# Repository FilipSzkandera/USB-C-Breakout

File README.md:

# USB-C Breakout board

I have searched a few places on internet and wasn't able to find a small, cheap and breadboard friendly USB-C adapter that I would like, so I made my own.
It has a neat fanout of all the USB-C pins (without the shield), which are nicely labeled for a very easy use while prototyping.

## Possible usecases:
#### On breadboard:

#### Directly on a prototyping board or a PCB:

## Check out my other PCBs:

- **ESP32-C3 Nano** (in collaboration with [@frycaktadeas](https://github.com/frycaktadeas/)): https://github.com/frycaktadeas/esp32-c3

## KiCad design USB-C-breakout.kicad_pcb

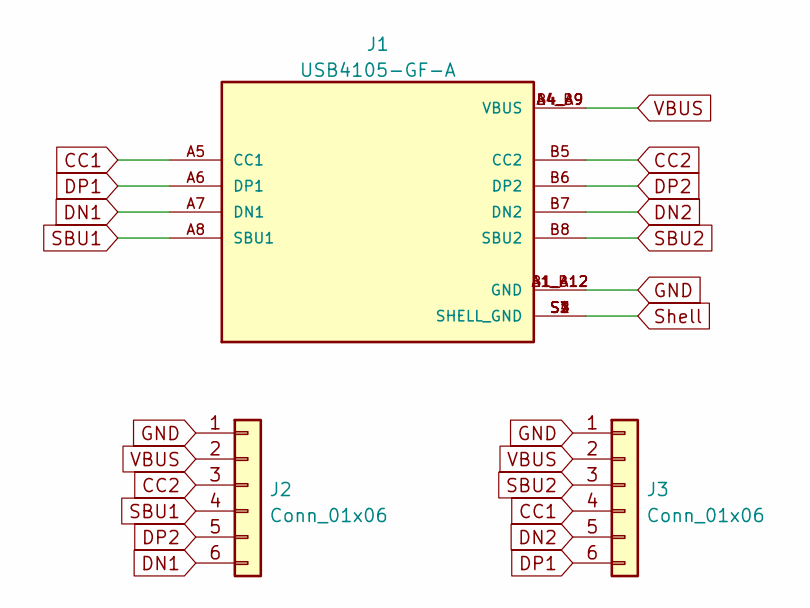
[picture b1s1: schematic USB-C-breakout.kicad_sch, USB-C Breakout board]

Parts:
J1: USB4105-GF-A; GCT_USB4105-GF-A; PARTREV A3
J2, J3: Conn_01x06; PinHeader_1x06_P2.54mm_Vertical

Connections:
CC1: J1.A5 (CC1), J3.4
CC2: J1.B5 (CC2), J2.3
DN1: J1.A7 (DN1), J2.6
DN2: J1.B7 (DN2), J3.5
DP1: J1.A6 (DP1), J3.6
DP2: J1.B6 (DP2), J2.5
GND: J1.A1_B12 (GND), J1.B1_A12 (GND), J2.1, J3.1
SBU1: J1.A8 (SBU1), J2.4
SBU2: J1.B8 (SBU2), J3.3
Shell: J1.S1 (SHELL_GND), J1.S2 (SHELL_GND), J1.S3 (SHELL_GND), J1.S4 (SHELL_GND)
VBUS: J1.A4_B9 (VBUS), J1.B4_A9 (VBUS), J2.2, J3.2

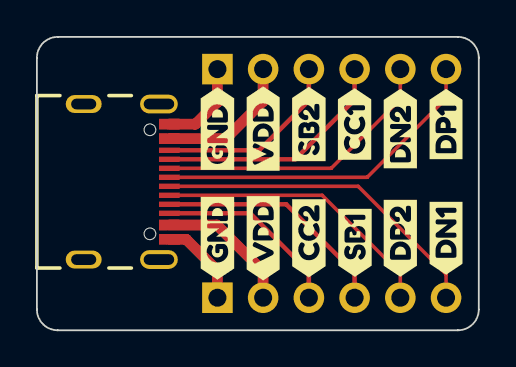
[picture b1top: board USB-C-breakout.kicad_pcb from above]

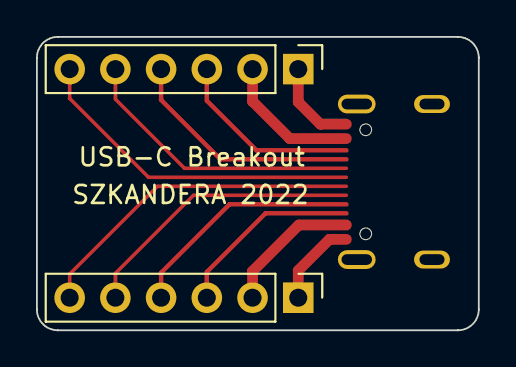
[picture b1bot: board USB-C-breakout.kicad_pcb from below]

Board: 2 copper layers, 24.5 x 16.3 mm, 15 parts (2 on the bottom side), 11 nets.

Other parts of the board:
kibuzzard-62B9BCC1: G***; kibuzzard-62B9BCC1
kibuzzard-62B9BCFF: G***; kibuzzard-62B9BCFF
kibuzzard-62B9BD52: G***; kibuzzard-62B9BD52
kibuzzard-62B9BD67: G***; kibuzzard-62B9BD67
kibuzzard-62B9BD75: G***; kibuzzard-62B9BD75
kibuzzard-62B9BDB7: G***; kibuzzard-62B9BDB7
kibuzzard-62B9BDD1: G***; kibuzzard-62B9BDD1
kibuzzard-62B9BDF3: G***; kibuzzard-62B9BDF3
kibuzzard-62B9BE2F: G***; kibuzzard-62B9BE2F
kibuzzard-62B9BE07: G***; kibuzzard-62B9BE07
kibuzzard-62B9BE25: G***; kibuzzard-62B9BE25
kibuzzard-62B9C129: G***; kibuzzard-62B9C129

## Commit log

2022-08-04 Added KiCAD files
2022-08-05 Added docs
2022-08-05 Changed naming
2022-08-05 Improved image quality
